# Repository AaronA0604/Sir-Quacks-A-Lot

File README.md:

# Sir-Quacks-A-Lot
I made Sir Quacks-A-Lot because I know that the method of rubber duck debugging is really helpful for me, and I wanted to take it to the next level. Sir Quacks-A-Lot is a device that listens to the user talking through their problem, and then replies to them in short and prompting sentences to help the user figure out their problem.

This device works in a few simple steps. First it has an mic that 1. detects if you are speaking using a VAD model, and 2. if you are, records what you until you stop talking. It stores your recording on a microSD card. The next step is to translate the recording to text. It does this using an API key to access whisper-large-v3-turbo. Then groq outputs the text and the device sends the text through an API key to anthropic/claude-haiku-5.5. This LLM then reads the text and replies in a short and prompting message. The final step is a text to speech program that turns the reply into audio. This audio is then played through the amp and speaker, so the user can hear it.

# This is the schematic:

# This is the pcb. I shaped it like a duck to keep with the theme, but you can shape it however you like:

Here are the parts you need:
# Bill of Materials (BOM)

| Item | Qty | Supplier | Cost/item | Total Cost | Link |
|---|---:|---|---:|---:|---|
| ESP32-S3-DevKitC-1 (N8R8 version) | 1 | wottzentic | $18.99 | $18.99 | [Amazon](https://www.amazon.com/ESP32-S3-DevKitC-1-N8R8-Dual-Core-ESP32-S3-Arduino-ESP-IDF/dp/B0H6MHKJXN/) |
| MAX98357A I2S amplifier breakout module | 1 | GODIYMODULES | $6.88 | $6.88 | [Amazon](https://www.amazon.com/MAX98357-MAX98357A-Amplifier-Interface-Raspberry/dp/B0DPJRLMDJ/) |
| 4 Ohm 40mm Diameter 3W Full Range Audio Speaker | 1 | Gikfun | $8.99 | $8.99 | [Amazon](https://www.amazon.com/Gikfun-Speaker-Stereo-Loudspeaker-Arduino/dp/B01LN8ONG4/) |
| Micro SD Flash Memory Card 16GB | 1 | Patriot Memory | $9.99 | $9.99 | [Amazon](https://www.amazon.com/Patriot-Micro-Flash-Memory-Card/dp/B08KSTKGVX/) |
| Micro SD card reader module | 1 | WWZMDiB | $5.99 | $5.99 | [Amazon](https://www.amazon.com/WWZMDiB-Adater-Module-Support-Arduino/dp/B0B779R5TZ/) |
| INMP441 I2S microphone module | 1 | JESSINIE | $6.95 | $6.95 | [Amazon](https://www.amazon.com/JESSINIE-INMP441-Omnidirectional-Microphone-Module/dp/B0F9451N2L/) |
| Estimated total shipping | 1 | — | $0.00 | $0.00 | — |

## Total Cost

**$57.79** (excluding any additional taxes or fees)

# Firmware
The main firmware file is named Quacks_Code.ino, and it contains almost everything you need for the program to run. The certs.h file contains the certificates needed for the HTTP requests, so you will need to download that file as well.

I left out a file named secrets.h, which contains my wifi name and password, and the two API keys I used. You will need to make an identically named file that looks like this:
```
#pragma once
const char *WIFI_NAME = "wifi_name;
const char *WIFI_PASSWORD = "wifi_password";

const char *GROQ_API_KEY = "groq_api_key";
const char *HC_API_KEY = "hc_api_key";
```
You will need to fill this in with your own values. Use the same groq API key that I used and mentioned above, called whisper-large-v3-turbo. For the other API key, I used anthropic/claude-haiku-5.5, although this costs money, so if you don't want to spend anything, find another LLM that can 1. read messages 2. reply and 3. be configured to give a specific kind of reply. If you change this model, you will need to change the model name in the Quacks_Code.ino file. Command+F the current model to find what to change.

This program also uses two libaries which you will need to download. To do this, first download the groq_stt and ESP32-audioI2S-master zip files. Then, in ArduinoIDE, go to Sketch -> Include Library -> Add .ZIP Library -> select the zip files.

I hope you enjoy this project!

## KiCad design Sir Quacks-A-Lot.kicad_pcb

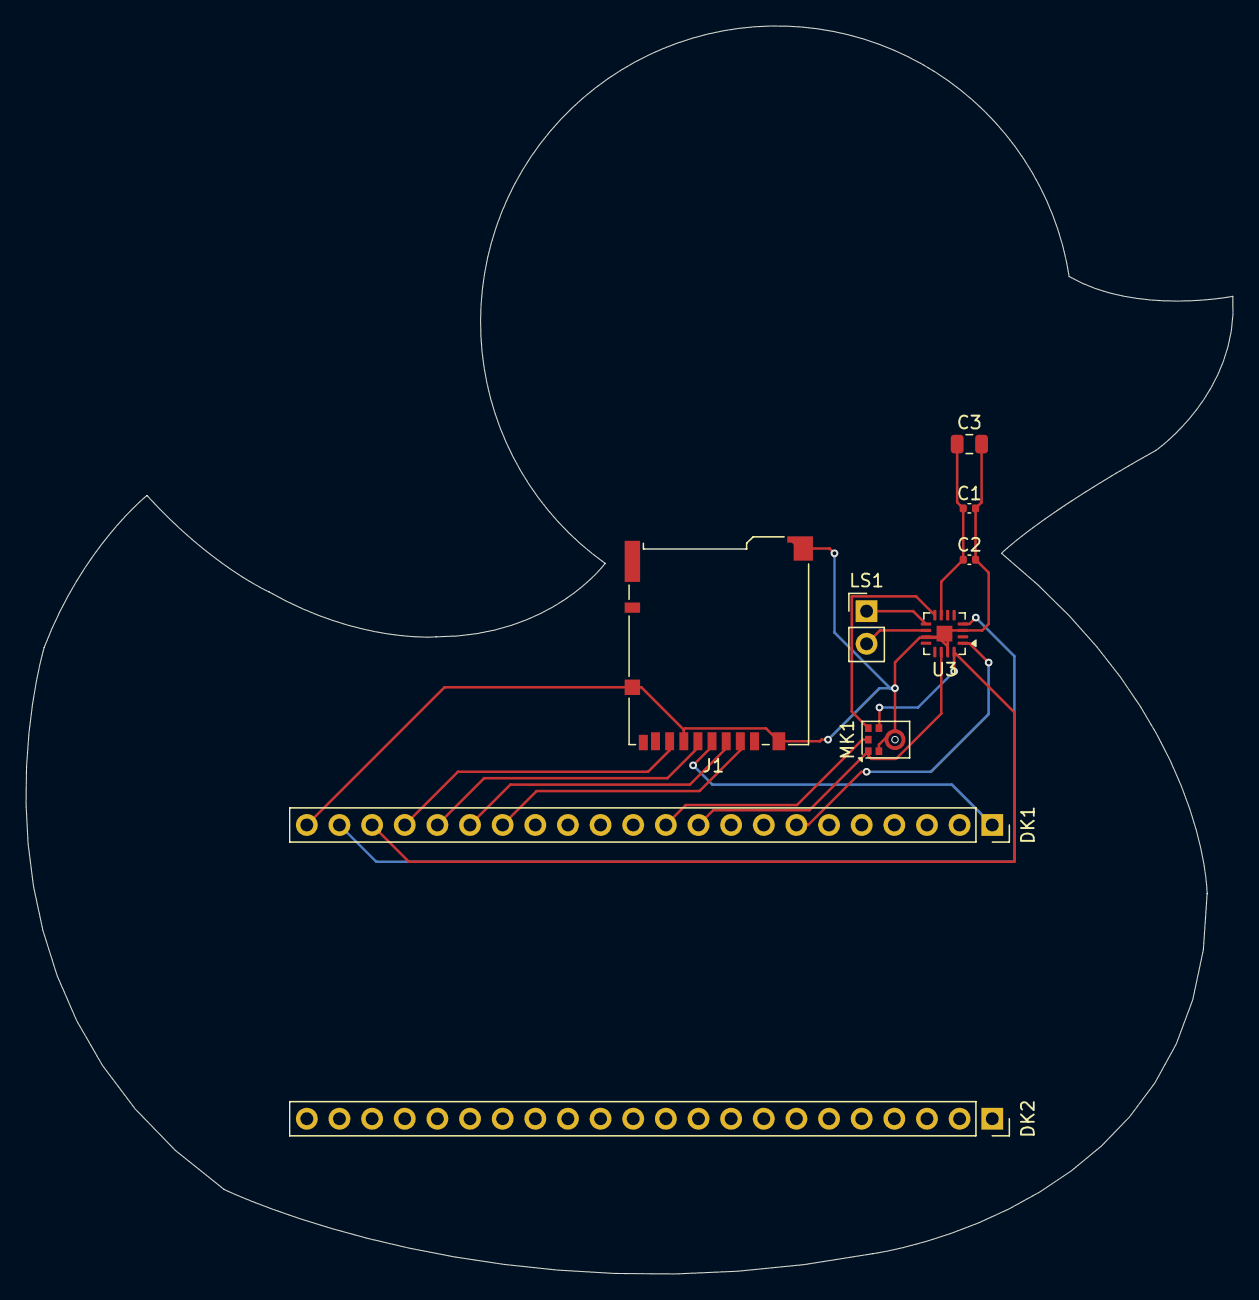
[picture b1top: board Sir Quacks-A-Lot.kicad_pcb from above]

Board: 2 copper layers, 93.9 x 97.1 mm, 9 parts (0 on the bottom side), 14 nets.

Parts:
C1, C2: 0.1uF; C_0402_1005Metric
C3: 10uF; C_0805_2012Metric
DK1, DK2: Conn_01x22_Pin; PinSocket_1x22_P2.54mm_Vertical
J1: Micro_SD_Card; microSD_HC_Hirose_DM3BT-DSF-PEJS
LS1: Speaker; PinHeader_1x02_P2.54mm_Vertical
MK1: ICS-43434; InvenSense_ICS-43434-6_3.5x2.65mm
U3: MAX98357A; TQFN-16-1EP_3x3mm_P0.5mm_EP1.23x1.23mm

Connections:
+3.3V: C1.1, C2.1, C3.1, MK1.5 (VDD), U3.7 (VDD), U3.8 (VDD)
+3V3: DK1.1, J1.4 (VDD)
+5V: DK1.21, U3.4 (~SD_MODE)
/DIN: DK1.7, U3.1 (DIN)
/MIC_SD: DK1.11, MK1.6 (SD)
/SCK: DK1.20, MK1.4 (SCK), U3.16 (BCLK)
/SD_CS: DK1.16, J1.2 (DAT3/CD)
/SD_MISO: DK1.19, J1.7 (DAT0)
/SD_MOSI: DK1.17, J1.3 (CMD)
/SD_SCK: DK1.18, J1.5 (CLK)
/WS: DK1.10, MK1.1 (WS), U3.14 (LRCLK)
GND: C1.2, C2.2, C3.2, DK1.22, J1.6 (VSS), J1.SH (SHIELD), MK1.2 (LR), MK1.3 (GND), U3.3 (GND), U3.11 (GND), U3.15 (GND), U3.17 (PAD)
unnamed: LS1.2, U3.10 (OUTN)
unnamed: LS1.1, U3.9 (OUTP)
